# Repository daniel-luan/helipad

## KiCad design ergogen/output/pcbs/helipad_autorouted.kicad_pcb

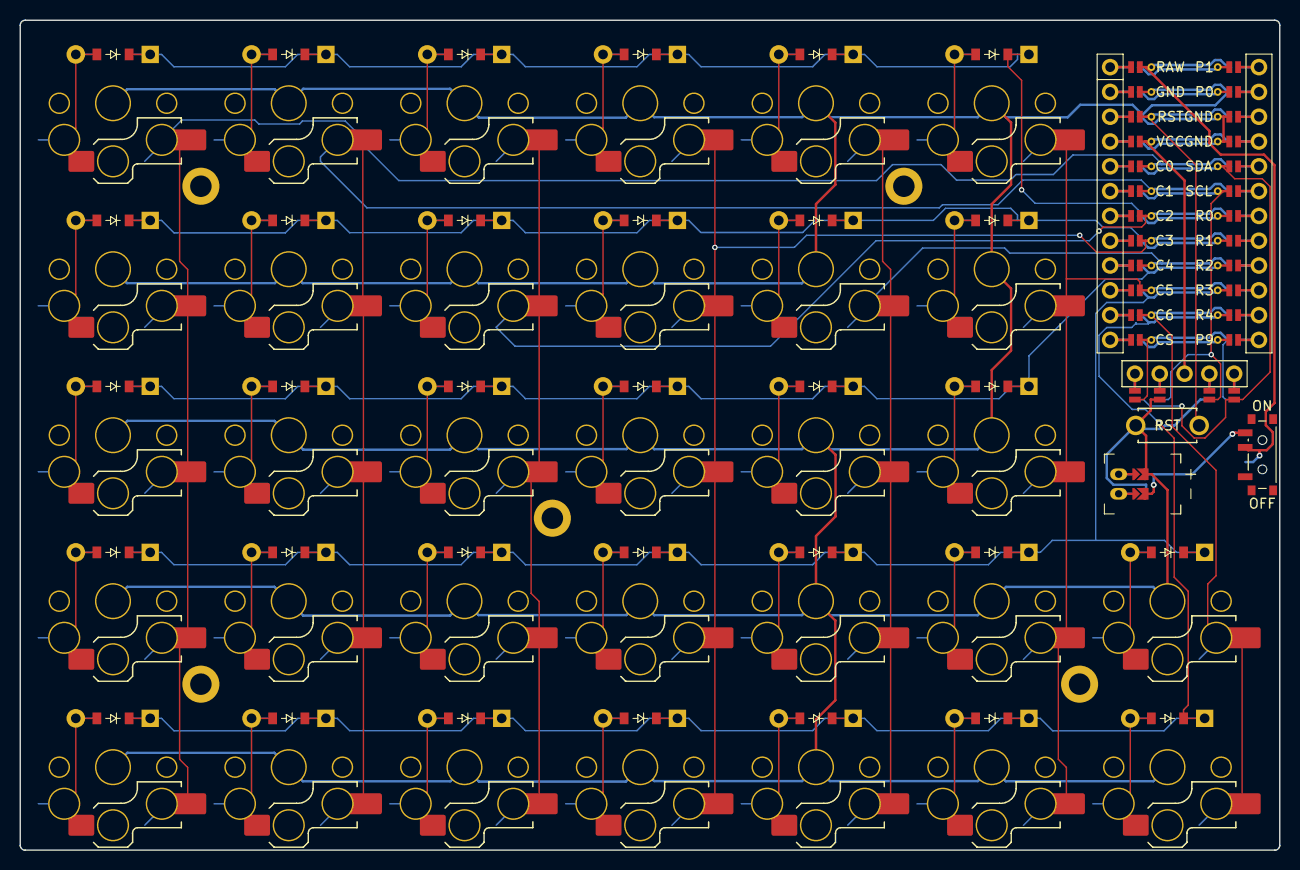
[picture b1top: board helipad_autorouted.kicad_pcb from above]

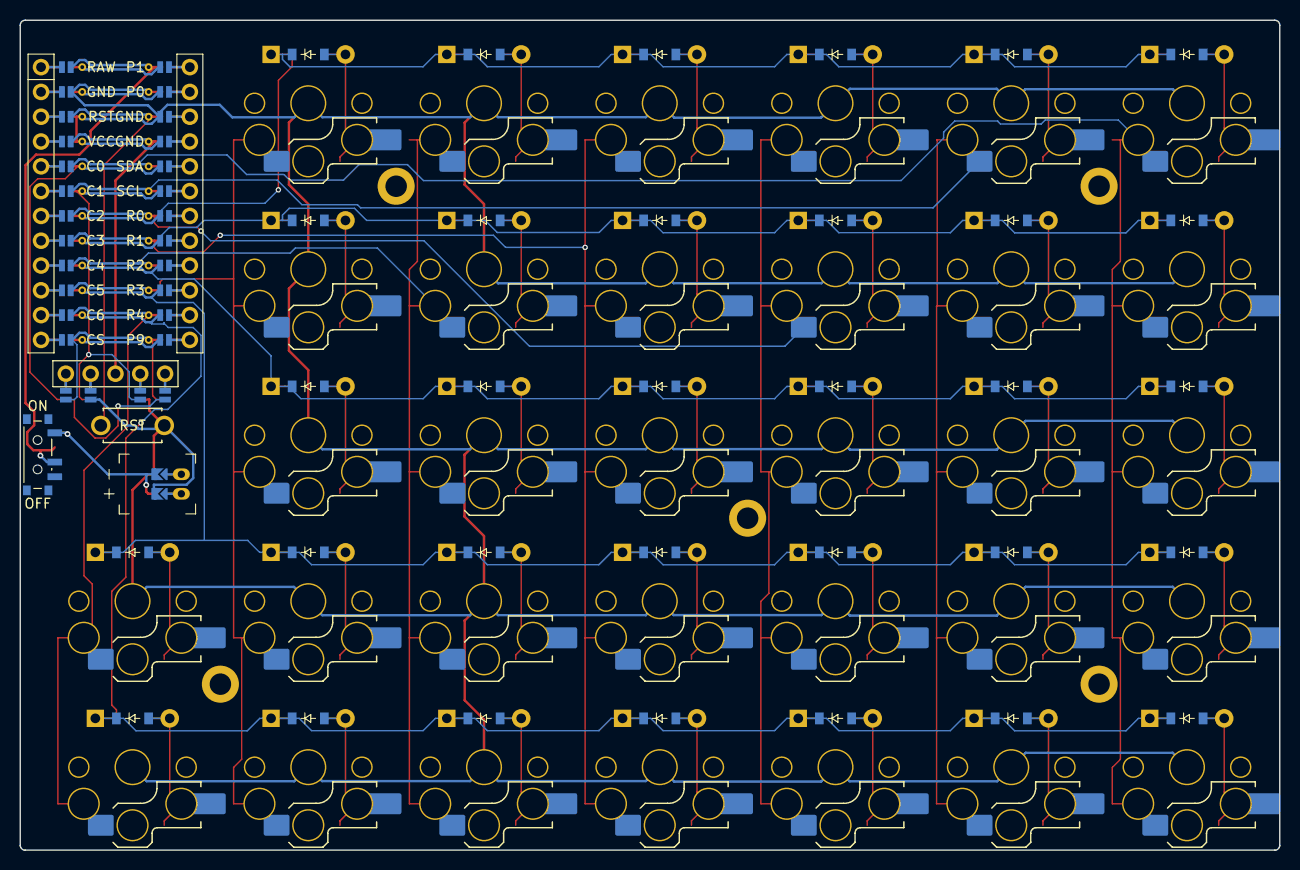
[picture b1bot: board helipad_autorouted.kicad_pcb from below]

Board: 2 copper layers, 129.0 x 85.0 mm, 74 parts (64 on the bottom side), 70 nets.

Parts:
D1, D2, D3, D4, D5, D6, D7, D8, D9, D10, D11, D12, D13, D14, D15, D16, D17, D18, D19, D20, D21, D22, D23, D24, D25, D26, D27, D28, D29, D30, D31, D32: diode_tht_sod123
DISP1: display_nice_view
H1, H2, H3, H4, H5: mounting_hole_plated
JST1: battery_connector_jst_ph_2
MCU1: mcu_nice_nano
PWR1: power_switch_smd_side
RST1: reset_switch_tht_top
S1, S2, S3, S4, S5, S6, S7, S8, S9, S10, S11, S12, S13, S14, S15, S16, S17, S18, S19, S20, S21, S22, S23, S24, S25, S26, S27, S28, S29, S30, S31, S32: switch_choc_v1_v2

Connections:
BAT_P: JST1.1, PWR1.1, PWR1.3
C0: MCU1.120, S1.1, S2.1, S3.1, S4.1, S5.1
C1: MCU1.119, S6.1, S7.1, S8.1, S9.1, S10.1
C2: MCU1.118, S11.1, S12.1, S13.1, S14.1, S15.1
C3: MCU1.117, S16.1, S17.1, S18.1, S19.1, S20.1
C4: MCU1.116, S21.1, S22.1, S23.1, S24.1, S25.1
C5: MCU1.115, S26.1, S27.1, S28.1, S29.1, S30.1
C6: MCU1.114, S31.1, S32.1
CS: DISP1.10, DISP1.20, MCU1.113
DISP1_1: DISP1.1, DISP1.14, DISP1.27
DISP1_2: DISP1.2, DISP1.15, DISP1.26
DISP1_4: DISP1.4, DISP1.16, DISP1.25
DISP1_5: DISP1.5, DISP1.17, DISP1.24
GND: DISP1.11, DISP1.21, JST1.2, MCU1.103, MCU1.104, MCU1.123, RST1.2
JST1_1: JST1.11, JST1.21, JST1.31
JST1_2: JST1.12, JST1.22, JST1.32
MCU1_1: MCU1.1, MCU1.24
MCU1_2: MCU1.2, MCU1.23
MCU1_3: MCU1.3, MCU1.22
MCU1_4: MCU1.4, MCU1.21
MCU1_5: MCU1.5, MCU1.20
MCU1_6: MCU1.6, MCU1.19
MCU1_7: MCU1.7, MCU1.18
MCU1_8: MCU1.8, MCU1.17
MCU1_9: MCU1.9, MCU1.16
MCU1_10: MCU1.10, MCU1.15
MCU1_11: MCU1.11, MCU1.14
MCU1_12: MCU1.12, MCU1.13
R0: D5.1, D10.1, D15.1, D20.1, D25.1, D30.1, MCU1.107
R1: D4.1, D9.1, D14.1, D19.1, D24.1, D29.1, MCU1.108
R2: D3.1, D8.1, D13.1, D18.1, D23.1, D28.1, MCU1.109
R3: D2.1, D7.1, D12.1, D17.1, D22.1, D27.1, D32.1, MCU1.110
R4: D1.1, D6.1, D11.1, D16.1, D21.1, D26.1, D31.1, MCU1.111
RAW: MCU1.124, PWR1.2
RST: MCU1.122, RST1.1
SCL: DISP1.12, DISP1.22, MCU1.106
SDA: DISP1.13, DISP1.23, MCU1.105
VCC: DISP1.3, MCU1.121
extraInner_bottom: D32.2, S32.2
extraInner_mod: D31.2, S31.2
index_bottom: D22.2, S22.2
index_home: D23.2, S23.2
index_mod: D21.2, S21.2
index_num: D25.2, S25.2
index_top: D24.2, S24.2
inner_bottom: D27.2, S27.2
inner_home: D28.2, S28.2
inner_mod: D26.2, S26.2
inner_num: D30.2, S30.2
inner_top: D29.2, S29.2
middle_bottom: D17.2, S17.2
middle_home: D18.2, S18.2
middle_mod: D16.2, S16.2
middle_num: D20.2, S20.2
middle_top: D19.2, S19.2
outer_bottom: D2.2, S2.2
outer_home: D3.2, S3.2
outer_mod: D1.2, S1.2
outer_num: D5.2, S5.2
outer_top: D4.2, S4.2
pinky_bottom: D7.2, S7.2
pinky_home: D8.2, S8.2
pinky_mod: D6.2, S6.2
pinky_num: D10.2, S10.2
pinky_top: D9.2, S9.2
ring_bottom: D12.2, S12.2
ring_home: D13.2, S13.2
ring_mod: D11.2, S11.2
ring_num: D15.2, S15.2
ring_top: D14.2, S14.2

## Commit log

2024-10-28 remove ergogen output
2024-10-28 don't build stls by default
2024-10-28 Add helix config.yaml
2024-10-28 generate gerber for manually_routed and autorouted pcbs
2024-10-28 Add ergogen output
2024-10-28 Update manually routed pcb
